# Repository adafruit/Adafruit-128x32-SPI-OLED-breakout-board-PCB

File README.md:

# Monochrome 128x32 SPI OLED graphic display

<a href="http://www.adafruit.com/products/661"><br/>Click here to purchase one from the Adafruit shop</a>

These displays are small, only about 1" diagonal, but very readable due to the high contrast of an OLED display. This display is made of 128x32 individual white OLED pixels, each one is turned on or off by the controller chip. Because the display makes its own light, no backlight is required. This reduces the power required to run the OLED and is why the display has such high contrast; we really like this miniature display for its crispness!

The driver chip SSD1306, __communicates via SPI only__. 4 or 5 pins are required to communicate with the chip in the OLED display.

The OLED and driver require a 3.3V power supply and 3.3V logic levels for communication. To make it easier for our customers to use, we've added a 3.3v regulator and level shifter on board! This makes it compatible with any 5V microcontroller, such as the Arduino.

The power requirements depend a little on how much of the display is lit but on average the display uses about 20mA from the 3.3V supply. Built into the OLED driver is a simple switch-cap charge pump that turns 3.3v-5v into a high voltage drive for the OLEDs, making it one of the easiest ways to get an OLED into your project!

Of course, we wouldn't leave you with a datasheet and a "good luck": [We have a detailed tutorial](http://learn.adafruit.com/monochrome-oled-breakouts) and [example code in the form of an Arduino library](https://github.com/adafruit/Adafruit_SSD1306) for text and graphics. You'll need a microcontroller with more than 512 bytes of RAM since the display must be buffered.

You can download our SSD1306 OLED display Arduino library from github which comes with example code. The library can print text, bitmaps, pixels, rectangles, circles and lines. It uses 512 bytes of RAM since it needs to buffer the entire display but its very fast! The code is simple to adapt to any other microcontroller.

### License

Adafruit invests time and resources providing this open source design, please support Adafruit and open-source hardware by purchasing products from [Adafruit](https://www.adafruit.com)!

Designed by Limor Fried/Ladyada for Adafruit Industries.

Creative Commons Attribution/Share-Alike, all text above must be included in any redistribution. See license.txt for additional details.

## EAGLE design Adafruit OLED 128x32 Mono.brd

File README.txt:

This is the PCB for the Adafruit 128x32 SPI OLED breakout board
Format is EagleCAD schematic and board layout

For more details, check out the product page at

-----> http://www.adafruit.com/products/661

Adafruit invests time and resources providing this open source design, 
please support Adafruit and open-source hardware by purchasing 
products from Adafruit!

Designed by Adafruit Industries.  
Creative Commons Attribution, Share-Alike license, check license.txt for more information
All text above must be included in any redistribution

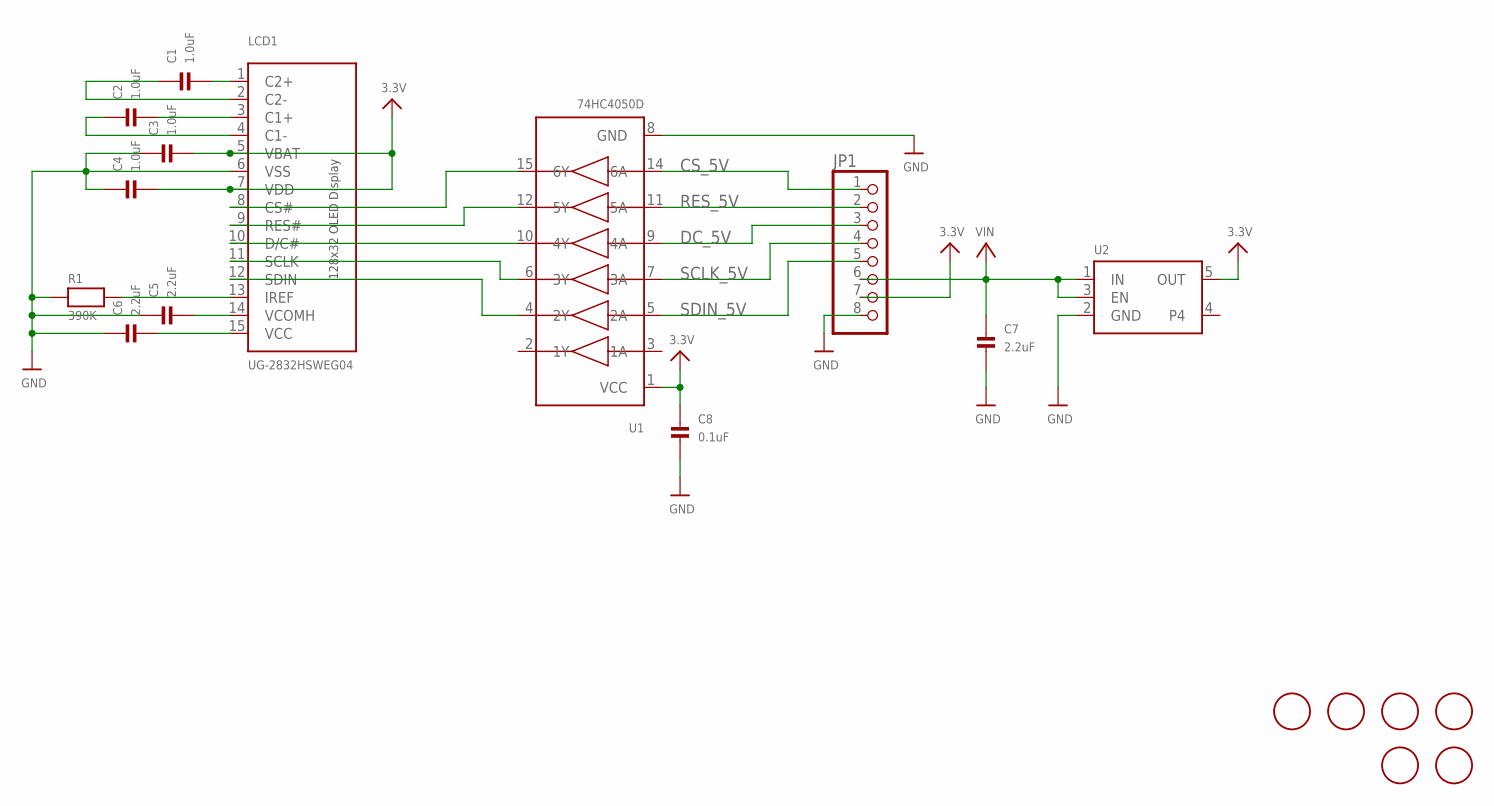
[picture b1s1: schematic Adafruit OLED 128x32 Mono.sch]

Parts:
C1, C2, C3, C4: 1.0uF; 0805
C5, C6, C7: 2.2uF; 0805
C8: 0.1uF; 0805
JP1: HEADER-1X876MIL; 1X08_ROUND_76
LCD1: UG-2832HSWEG04; UG-2832HSWEG04_WRAPAROUND
R1: 390K; 0805
U1: 74HC4050D; SOIC16
U2: VREG_SOT23-5; SOT23-5
U$2, U$3, U$4, U$5: MOUNTINGHOLE2.0; MOUNTINGHOLE_2.0_PLATED
U$6, U$7: FIDUCIAL; FIDUCIAL_1MM

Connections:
3.3V: C3.2, C4.2, C8.1, JP1.7, LCD1.5 (VBAT), LCD1.7 (VDD), U1.1 (VCC), U2.5 (OUT)
CS_5V: JP1.1, U1.14 (6A)
DC_5V: JP1.3, U1.9 (4A)
GND: C3.1, C4.1, C5.1, C6.1, C7.2, C8.2, JP1.8, LCD1.6 (VSS), R1.1, U1.8 (GND), U2.2 (GND)
unnamed: C1.1, LCD1.2 (C2-)
unnamed: C1.2, LCD1.1 (C2+)
unnamed: C2.1, LCD1.4 (C1-)
unnamed: C2.2, LCD1.3 (C1+)
unnamed: LCD1.8 (CS#), U1.15 (6Y)
unnamed: LCD1.13 (IREF), R1.2
unnamed: C5.2, LCD1.14 (VCOMH)
unnamed: LCD1.9 (RES#), U1.12 (5Y)
unnamed: LCD1.10 (D/C#), U1.10 (4Y)
unnamed: LCD1.11 (SCLK), U1.6 (3Y)
unnamed: LCD1.12 (SDIN), U1.4 (2Y)
unnamed: C6.2, LCD1.15 (VCC)
RES_5V: JP1.2, U1.11 (5A)
SCLK_5V: JP1.4, U1.7 (3A)
SDIN_5V: JP1.5, U1.5 (2A)
VIN: C7.1, JP1.6, U2.1 (IN), U2.3 (EN)

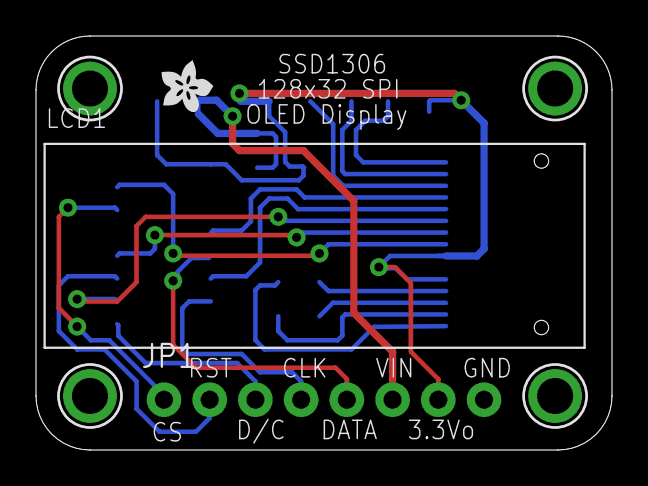
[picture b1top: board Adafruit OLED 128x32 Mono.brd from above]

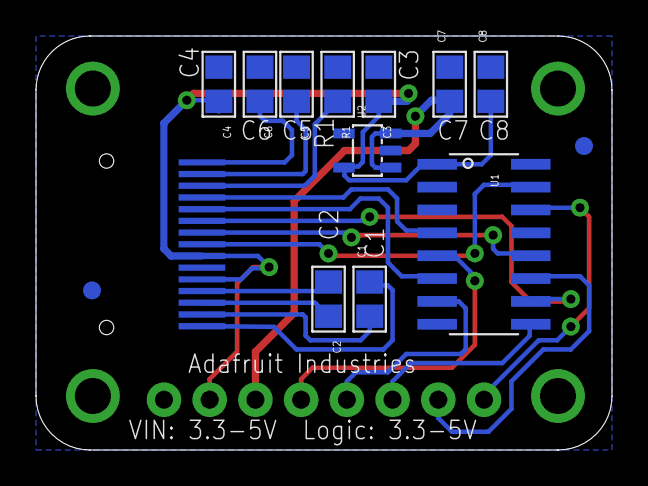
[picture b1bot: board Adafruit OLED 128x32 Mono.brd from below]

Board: 2 copper layers, 32.0 x 23.0 mm, 20 parts (13 on the bottom side), 20 nets.

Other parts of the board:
U$10: ADAFRUIT200MIL

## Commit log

2012-03-08 woot!
2012-03-08 fixed typos
2019-04-03 image + readme
2026-06-03 update file format to XML
